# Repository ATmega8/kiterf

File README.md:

# _KiteRF_

_KiteRF is a SDR system with K210 & FPGA & ESP32 as its core controller, which make SDR more intelligent, portable and cheap._

* KiteRF Structure

  * DS (Digital Signal) unit

    * FPGA (Field-Programmable Gate Array)

      * Radio Frequency Data Processing

      * DS Control

      * Communication with PC

    * K210 (Kendryte K210)

      * LCD control

      * Camera control

      * Audio

      * FFT

    * ESP32 (Espressif ESP32)

      * Wi-Fi Data Transmission

      * SDCARD control

      * Touch Button

      * RGB LED Control

  * RF (Radio Frequency) unit

    * ADC (Analog-to-Digital Converter)
    
      * Sampling Analog Baseband IQ Data

    * DAC (Digital-to-Analog Converter)

      * Output Analog Baseband IQ Data 

    * RF Transceiver

      * Mixing IF signal to baseband and outputting IQ analog signal

    * VCO (Voltage-Controlled Oscillator)

      * Provide local IF frequency

    * Mixer (Frequency mixer)

      * Mixing HF signal to IF signal

    * LNA (Low-Noise Amplifier)

      * Suppression of Mirror Noise Signal

    * RF Switch

      * Switching signal paths in different frequencies

* KiteRF core-board v1.0.0

## Contents

* Directory tree

    ```
    ├── add_path.sh
    ├── data
    │   ├── kendryte_datasheet.pdf
    │   ├── kendryte_freertos_programming_guide.pdf
    │   ├── kiterf_1.0.0.jpg
    │   ├── kiterf_structure.pos
    │   └── kiterf_structure.svg
    ├── docs
    │   └── Doxyfile
    ├── LICENSE
    ├── project
    │   ├── code
    │   │   ├── ESP32
    │   │   ├── ESP8266
    │   │   └── K210
    │   └── pcb
    │       ├── K210
    │       └── RF
    ├── README.md
    └── tools
        ├── cmake-3.14.2
        ├── ESP32
        │   └── esp-idf
        ├── ESP8266
        │   ├── ESP8266_RTOS_SDK
        │   └── xtensa-lx106-elf
        └── K210
            ├── kendryte-freertos-sdk
            ├── kendryte-toolchain
            └── kflash
    ```

    * project

      * PCB project (KiCAD)

      * FPGA project (ISE)

      * ESP32 project (esp-idf)

      * K210 project (Kendryte FreeRTOS)

    * release

      * PCB Gerber

      * FPGA bin

      * ESP32 bin

      * K210 bin

    * tools

      * script

      * SDK

      * toolchain

## How to use

You can follow the steps below to set up the development environment, or directly download the release version of the full environment.

* clone

  ```bash
  git clone --recursive https://github.com/ATmega8/kiterf
  cd kiterf
  ```

  * note

    Don't omit `--recursive`, because we use submodule.

* update

  ```bash
  git pull
  git submodule update --init --recursive
  ```

* Add environment variables

  ```bash
  . add_path.sh
  ```
  * note

    Don't forget `"."`

* Install toolchain

  * K210

    * Ubuntu/Debian/Kali

      ```bash
      wget https://www.kiterf.xyz/download/kendryte-toolchain-ubuntu-amd64-8.2.0-20190213.tar.gz
      tar zxvf kendryte-toolchain-ubuntu-amd64-8.2.0-20190213.tar.gz -C tools/K210/
      rm kendryte-toolchain-ubuntu-amd64-8.2.0-20190213.tar.gz
      ```
    
    * Arch

      ```bash
      wget https://www.kiterf.xyz/download/kendryte-toolchain-arch-amd64-8.2.0-20190415.tar.gz
      tar zxvf kendryte-toolchain-arch-amd64-8.2.0-20190415.tar.gz -C tools/K210/
      rm kendryte-toolchain-arch-amd64-8.2.0-20190415.tar.gz
      ```

  * ESP32

    * Ubuntu/Debian/Kali/Arch

      ```bash
      cd tools/ESP32/esp-idf
      ./install.sh
      cd $KITERF_PATH
      ```

  * ESP8266

    KiteRF also integrates the ESP8266 development environment, which is not necessary, and you can choose to ignore it.

    * Ubuntu/Debian/Kali/Arch

      ```bash
      wget https://www.kiterf.xyz/download/xtensa-lx106-elf-linux64-1.22.0-92-g8facf4c-5.2.0.tar.gz
      tar zxvf xtensa-lx106-elf-linux64-1.22.0-92-g8facf4c-5.2.0.tar.gz -C tools/ESP8266/
      rm xtensa-lx106-elf-linux64-1.22.0-92-g8facf4c-5.2.0.tar.gz
      ```

  * CMake

    * Ubuntu/Debian/Kali/Arch

      ```bash
      wget https://www.kiterf.xyz/download/cmake-3.14.2.tar.gz
      tar xf cmake-3.14.2.tar.gz -C tools/
      cd tools/cmake-3.14.2
      ./configure
      # Please do not use all CPU cores to compile, otherwise your computer may crash.
      make -j2
      cd $KITERF_PATH
      rm cmake-3.14.2.tar.gz
      ```

## Release

* download

  ```bash
  wget https://www.kiterf.xyz/download/kiterf-debain-amd64-1.2.0-20190517.tar.gz
  tar zxvf kiterf-debain-amd64-1.2.0-20190517.tar.gz
  rm kiterf-debain-amd64-1.2.0-20190517.tar.gz
  cd kiterf
  ```
* Add environment variables

  ```bash
  . add_path.sh
  ```
  * note

    Don't forget `"."`

## License

* MIT License
 
  A short and simple permissive license with conditions only requiring preservation of copyright and license notices. Licensed works, modifications, and larger works may be distributed under different terms and without source code.

## Contributing

If you want to support this project, we hope you can contribute your code or circuit.

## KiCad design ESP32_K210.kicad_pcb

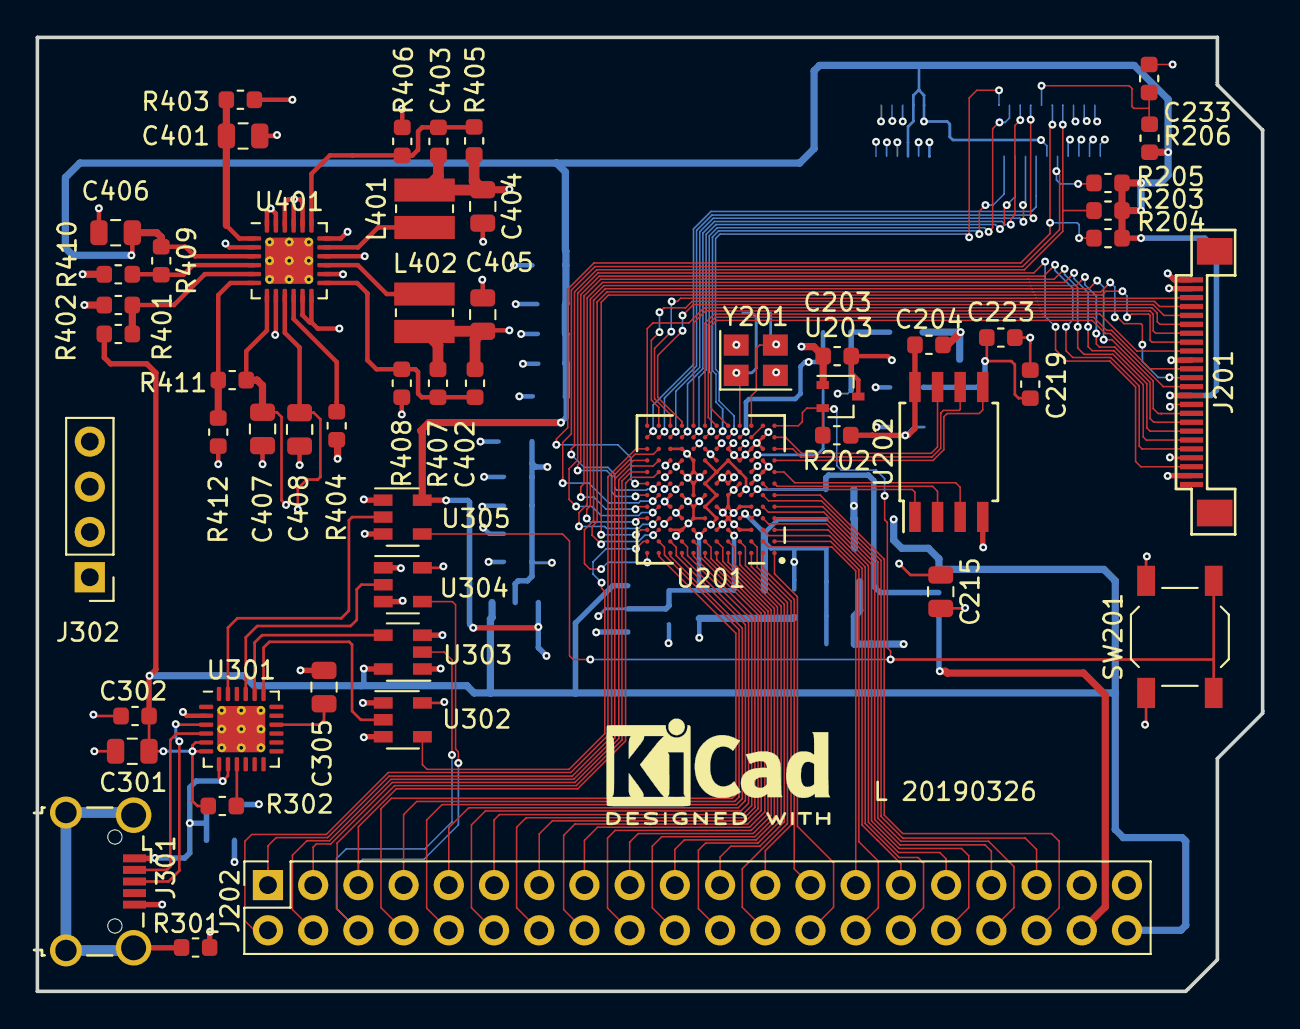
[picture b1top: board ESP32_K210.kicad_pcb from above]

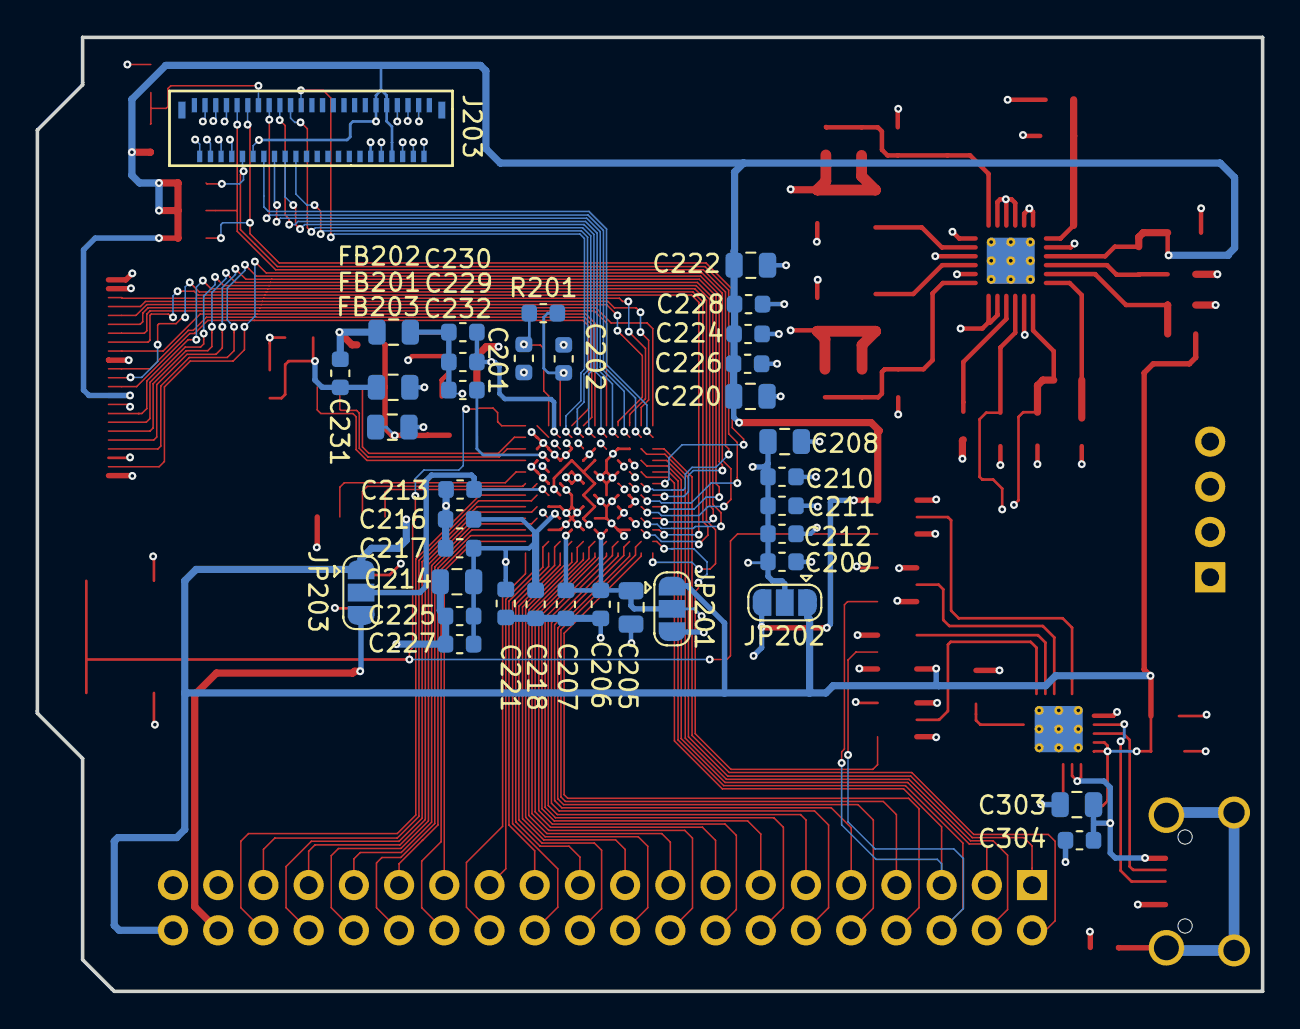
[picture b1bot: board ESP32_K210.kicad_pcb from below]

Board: 4 copper layers, 68.8 x 53.6 mm, 90 parts (37 on the bottom side), 106 nets.

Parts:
C201, C202: 10p; C_0603_1608Metric
C203, C204, C206, C207, C209, C210, C211, C212, C213, C216, C217, C218, C219, C221, C223, C224, C225, C226, C227, C228, C229, C232: 0.1uF; C_0603_1608Metric
C205, C208, C214, C215, C220, C222, C301, C303, C305: 4.7uF; C_0805_2012Metric
C230, C231: 4.7uF; C_0603_1608Metric
C233: 1uF; C_0603_1608Metric
C302, C304: 0.1u; C_0603_1608Metric
C401: 1u; C_0805_2012Metric
C402, C403: 47p; C_0603_1608Metric
C404: 10u; C_0805_2012Metric
C405: 10uF; C_0805_2012Metric
C406, C407, C408: 4.7u; C_0805_2012Metric
FB201, FB202, FB203: 600R@100MHz; L_0805_2012Metric
J201: Camera; FPC_24
J202: Conn_02x20_Odd_Even; PinSocket_2x20_P2.54mm_Vertical
J203: LCD; FH26-xxS-0.3SHW
J301: USB_OTG; USB_Micro-B_Wuerth_629105150521_CircularHoles
J302: Conn_01x04; PinHeader_1x04_P2.54mm_Vertical
JP201: IO18-IO35; SolderJumper-3_P1.3mm_Open_RoundedPad1.0x1.5mm
JP202: IO0-IO17; SolderJumper-3_P1.3mm_Open_RoundedPad1.0x1.5mm
JP203: IO36-IO47; SolderJumper-3_P1.3mm_Open_RoundedPad1.0x1.5mm
L401: 3.3uH; L_Wuerth_MAPI-3015
L402: 2.2uH; L_Wuerth_MAPI-3010
R201, R301: 1M; R_0603_1608Metric
R202, R206, R404: 100K; R_0603_1608Metric
R203, R204, R205: 10K; R_0603_1608Metric
R302: 4K7; R_0603_1608Metric
R401: 33K; R_0603_1608Metric
R402: 68K; R_0603_1608Metric
R403: 1R; R_0603_1608Metric
R405: 680K; R_0603_1608Metric
R406, R407: 150K; R_0603_1608Metric
R408, R410: 300K; R_0603_1608Metric
R409: 240K; R_0603_1608Metric
R411: 360K; R_0603_1608Metric
R412: 200K; R_0603_1608Metric
SW201: RESET; SW_SPST_TL3342
U201: K210; BGA-144_12x12_8.0x8.0mm
U202: W25Q64FW; SOIJ-8_5.3x5.3mm_P1.27mm
U203: MAX803; SOT-323_SC-70
U301: CP2104; QFN-24-1EP_4x4mm_P0.5mm_EP2.7x2.6mm_ThermalVias
U302, U303, U304, U305: 74LVC1G125; SOT-23-5
U401: TPS650532; QFN-24-1EP_4x4mm_P0.5mm_EP2.7x2.6mm_ThermalVias
Y201: 26MHz 10ppm; Crystal_SMD_3225-4Pin_3.2x2.5mm

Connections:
+1V5: C408.1, J201.10, U401.9
+1V8: C204.1, C220.1, C222.1, C224.1, C226.1, C228.1, C406.1, FB203.1, J201.11, J202.38, J203.8, J203.9, J203.11, J203.34, JP201.3, JP202.3, JP203.3, R202.1, R203.1, R204.1, R205.1, R206.1, R409.1, U201.H3, U201.K6, U201.K8, U202.8, U305.5, U401.3
+2V8: C407.1, J201.4, R411.1, U401.7
+3V3: C203.1, C301.1, C302.1, C403.1, C404.1, J201.23, J202.40, J203.12, J203.44, JP201.1, JP202.1, JP203.1, L401.2, R302.1, R401.1, R405.1, U203.3, U301.5, U301.6, U302.5
+5V: C303.1, C304.1, J301.1, J302.1, J302.2, R403.2, R404.2, U301.7, U301.8, U401.2, U401.8, U401.11, U401.12, U401.16, U401.20, U401.21, U401.22
/K210/BOOT: U201.B12, U303.4
/K210/DB0: J203.32, U201.L12
/K210/DB1: J203.31, U201.L11
/K210/DB2: J203.30, U201.L10
/K210/DB3: J203.29, U201.L9
/K210/DB4: J203.28, U201.L8
/K210/DB5: J203.27, U201.L7
/K210/DB6: J203.26, U201.L6
/K210/DB7: J203.25, U201.L5
/K210/DVP-HREF: J201.9, U201.A12
/K210/DVP-PCLK: J201.17, U201.C12
/K210/DVP-PWDN: J201.8, U201.D12
/K210/DVP-RESET: J201.6, U201.E12
/K210/DVP-SIO_C: J201.5, U201.F12
/K210/DVP-SIO_D: J201.3, U201.E11
/K210/DVP-VSYNC: J201.7, U201.D11
/K210/DVP-XCLK: J201.13, U201.C11
/K210/DVP-Y2: J201.19, U201.M12
/K210/DVP-Y3: J201.21, U201.M11
/K210/DVP-Y4: J201.22, U201.M10
/K210/DVP-Y5: J201.20, U201.M9
/K210/DVP-Y6: J201.18, U201.M8
/K210/DVP-Y7: J201.16, U201.M7
/K210/DVP-Y8: J201.14, U201.M6
/K210/DVP-Y9: J201.12, U201.M5
/K210/FLASH_CLK: U201.K1, U202.6
/K210/FLASH_CS: U201.G2, U202.1
/K210/FLASH_D0: U201.J1, U202.5
/K210/FLASH_D1: U201.G1, U202.2
/K210/FLASH_D2: U201.H1, U202.3
/K210/FLASH_D3: U201.L1, U202.7
/K210/IO0: J202.1, U201.K11
/K210/IO1: J202.2, U201.K12
/K210/IO2: J202.3, U201.J11
/K210/IO3: J202.4, U201.J12
/K210/IO4: J202.5, U201.H11, U304.4
/K210/IO5: J202.6, U201.H12, U302.2
/K210/IO18: J202.7, U201.B11
/K210/IO19: J202.8, U201.A11
/K210/IO20: J202.9, U201.B10
/K210/IO21: J202.10, U201.A10
/K210/IO22: J202.11, U201.B9
/K210/IO23: J202.12, U201.A9
/K210/IO24: J202.13, U201.B8
/K210/IO25: J202.14, U201.A8
/K210/IO26: J202.15, U201.B7
/K210/IO27: J202.16, U201.A7
/K210/IO28: J202.17, U201.B6
/K210/IO29: J202.18, U201.A6
/K210/IO30: J202.19, U201.B5
/K210/IO31: J202.20, U201.A5
/K210/IO32: J202.21, U201.B4
/K210/IO33: J202.22, U201.A4
/K210/IO34: J202.23, U201.B3
/K210/IO35: J202.24, U201.A3
/K210/IO36: J202.25, U201.A2
/K210/IO37: J202.26, U201.A1
/K210/IO38: J202.27, U201.B2
/K210/IO39: J202.28, U201.B1
/K210/IO40: J202.29, U201.C2
/K210/IO41: J202.30, U201.C1
/K210/IO42: J202.31, U201.D2
/K210/IO43: J202.32, U201.D1
/K210/IO44: J202.33, U201.E2
/K210/IO45: J202.34, U201.E1
/K210/IO46: J202.35, U201.F2
/K210/IO47: J202.36, U201.F1
/K210/LCD-CS: J203.37, R203.2, U201.G11
/K210/LCD-DC: J203.36, R205.2, U201.F11
/K210/LCD-WR: J203.35, R204.2, U201.G12
/K210/RESET: R202.2, SW201.2, U201.M1, U203.2, U305.4
/K210/USB2UART/DTR: U301.23, U305.2
/K210/USB2UART/RTS: U301.19, U303.2
/K210/USB2UART/RXD: U301.20, U302.4
/K210/USB2UART/TXD: U301.21, U304.2
/K210/USB2UART/USB_D+: J301.3, U301.3
/K210/USB2UART/USB_D-: J301.2, U301.4
/K210/VB012: C205.1, C206.1, C207.1, JP201.2, U201.C5, U201.C7, U201.C8, U303.5, U304.5
/K210/VB67: C213.1, JP203.2, U201.D3, U201.F3
/K210/VB345: C208.1, C209.1, C210.1, C211.1, C212.1, JP202.2, U201.D10, U201.G10, U201.H10
GND: C201.2, C202.2, C203.2, C204.2, C205.2, C206.2, C207.2, C208.2, C209.2, C210.2, C211.2, C212.2, C213.2, C214.2, C215.2, C216.2, C217.2, C218.2, C219.2, C220.2, C221.2, C222.2, C223.2, C224.2, C225.2, C226.2, C227.2, C228.2, C231.2, C233.2, C301.2, C302.2, C303.2, C304.2, C305.2, C401.2, C404.2, C405.2, C406.2, C407.2, C408.2, FB202.1, J201.2, J201.15, J201.24, J202.37, J202.39, J203.2, J203.3, J203.4, J203.5, J203.6, J203.7, J203.10, J203.38, J203.39, J203.40, J203.41, J203.42, J203.43, J301.5, J302.3, J302.4, R301.2, R402.2, R406.2, R408.2, R410.2, R412.2, SW201.1, U201.C3, U201.C4, U201.C6, U201.C9, U201.C10, U201.D5, U201.D7, U201.D8, U201.E3, U201.E4, U201.E5, U201.E6, U201.E8, U201.E10, U201.F5, U201.F7, U201.F8, U201.F9, U201.F10, U201.G3, U201.G4, U201.G5, U201.G6, U201.G8, U201.H2, U201.H5, U201.H7, U201.H8, U201.H9, U201.J2, U201.J4, U201.J6, U201.J8, U201.J10, U201.K2, U201.K3, U201.K5, U201.K7, U201.K9, U201.K10, U201.L2, U202.4, U203.1, U301.2, U301.25, U302.1, U302.3, U303.1, U303.3, U304.1, U304.3, U305.1, U305.3, U401.14, U401.18, U401.23, U401.24, Y201.2, Y201.4
unnamed: C201.1, R201.2, U201.M4, Y201.1
unnamed: C202.1, R201.1, U201.M3, Y201.3
unnamed: C229.1, C230.1, FB201.2, U201.L4
unnamed: C229.2, C230.2, C232.2, FB202.2, U201.K4
unnamed: C232.1, FB203.2, U201.J3
unnamed: C233.1, J203.33, R206.2
unnamed: C305.1, U301.16
unnamed: C401.1, R403.1, U401.1
unnamed: C402.2, R407.2, R408.1, U401.13
unnamed: C403.2, R405.2, R406.1, U401.19
unnamed: J301.6, R301.1
unnamed: L401.1, U401.17
unnamed: L402.1, U401.15
unnamed: R302.2, U301.9
unnamed: R401.2, R402.1, U401.5
unnamed: R404.1, U401.10
unnamed: R409.2, R410.1, U401.4
unnamed: R411.2, R412.1, U401.6
unnamed: U201.L3, U201.M2
VCC: C214.1, C215.1, C216.1, C217.1, C218.1, C219.1, C221.1, C223.1, C225.1, C227.1, C231.1, C402.1, C405.1, FB201.1, L402.2, R407.1, U201.D4, U201.D6, U201.D9, U201.E7, U201.E9, U201.F4, U201.F6, U201.G7, U201.G9, U201.H4, U201.H6, U201.J5, U201.J7, U201.J9

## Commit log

2019-04-07 Init commit
2019-04-07 feature(README): add icons
2019-04-07 feature(license): add mit license
2019-04-07 bugfix(README): fix url error
2019-04-07 feature(README): add structure
2019-04-07 bugfix(README): fix some error
2019-04-10 feature(project): update structure
2019-04-10 feature(pcb/RF): update RF part schematic
2019-04-12 feature(k210): add k210 project
2019-04-13 feature(README): update README
2019-04-14 feature(pcb/RF): finished RF part schematic
2019-04-14 feature(esp32): add esp32 environment
2019-04-15 feature(toolchain): add k210 arch toolchain
2019-04-16 feature(pcb/RF): update RF part BOM
2019-04-16 bugfix(README):Fix some EN syntax problems :)
2019-04-17 feature(.gitignore):add ignore clion setting and build directory
2019-04-17 bugfix(PCB): fixed symbol libraries path.
2019-04-18 feature(mmo): port mmo
2019-04-18 feature(fir) add fir function from arm dsp library
2019-04-20 feature(ring_buf): add ESP32&K210 ring_buf
2019-04-20 feature(dsp): add ESP32&K210 dsp lib
2019-04-21 feature(travis): add travis-ci
2019-04-21 feature(pid): add ESP32&K210 pid library
2019-04-22 bugfix(README): delete version badge
2019-04-23 fixbug(k210/build.sh)
2019-04-23 feature(doxygen): doxygen test
2019-04-23 feature(travis): travis send to server kiterf.xyz
2019-05-10 feature(pcb/rf) fix some bug
2019-05-10 bugfix(code/K210)增加build.sh可执行权限
2019-05-11 feature(littlevgl): add lvgl gui
2019-05-12 feature(ESP32): add ESP32 lcd demo
2019-05-13 feature(cmake): add cmake 3.14.2 path
2019-05-14 feature(esp-idf): update esp-idf
2019-05-14 feature(travis): change download address
2019-05-14 feature(rf_spi): add rf_spi
2019-05-15 feature(rf_slave): Slave temporarily does not support subpacket transmission
2019-05-15 feature(flash_buf): add flash_buf
2019-05-17 feature(ESP8266): add ESP8266
2019-05-18 bugfix(add_path): fix
2019-07-06 feature(code): change path
2019-07-07 lcd ok
2019-07-08 bugfix(ram): fix buffer size error
2019-07-08 wifi and spiffs ok
2019-07-08 bugfix(travis): update travis
2019-07-10 encoder ok
2019-07-29 feature(INA219): add INA219
2020-01-14 feature(esp-idf): update idf to release/v4.0
2020-01-14 clean project
2020-01-14 feature(ESP32): add lua
2020-02-28 update last work
2020-03-01 add lcd hx8357 driver
2020-03-01 lcd_write_data 增加空指针判断
2020-03-02 add esp-dsp library
2020-03-05 add waterfall
2020-03-11 feature(esp32/hardware_drivers)
2020-03-19 add set_led, set_tuner_gan, set_tuner_frequency lua interface
2020-03-27 Set theme jekyll-theme-merlot
2020-03-27 feature(esp32/receive_spi_iq_data)
2020-03-27 add github pages
2020-03-27 Change github pages theme to jekyll-theme-console
2020-03-27 feature(docs/update github pages index.html)
2020-03-27 feature(docs/update github pages themes
2020-03-27 fixbug(docs/remove _config.yml relative_permalinks
2020-03-27 fixbug(docs/fixed missing css file
2020-03-27 feature(docs/update github pages themes)
2020-03-27 update theme config
2020-03-27 Create CNAME
